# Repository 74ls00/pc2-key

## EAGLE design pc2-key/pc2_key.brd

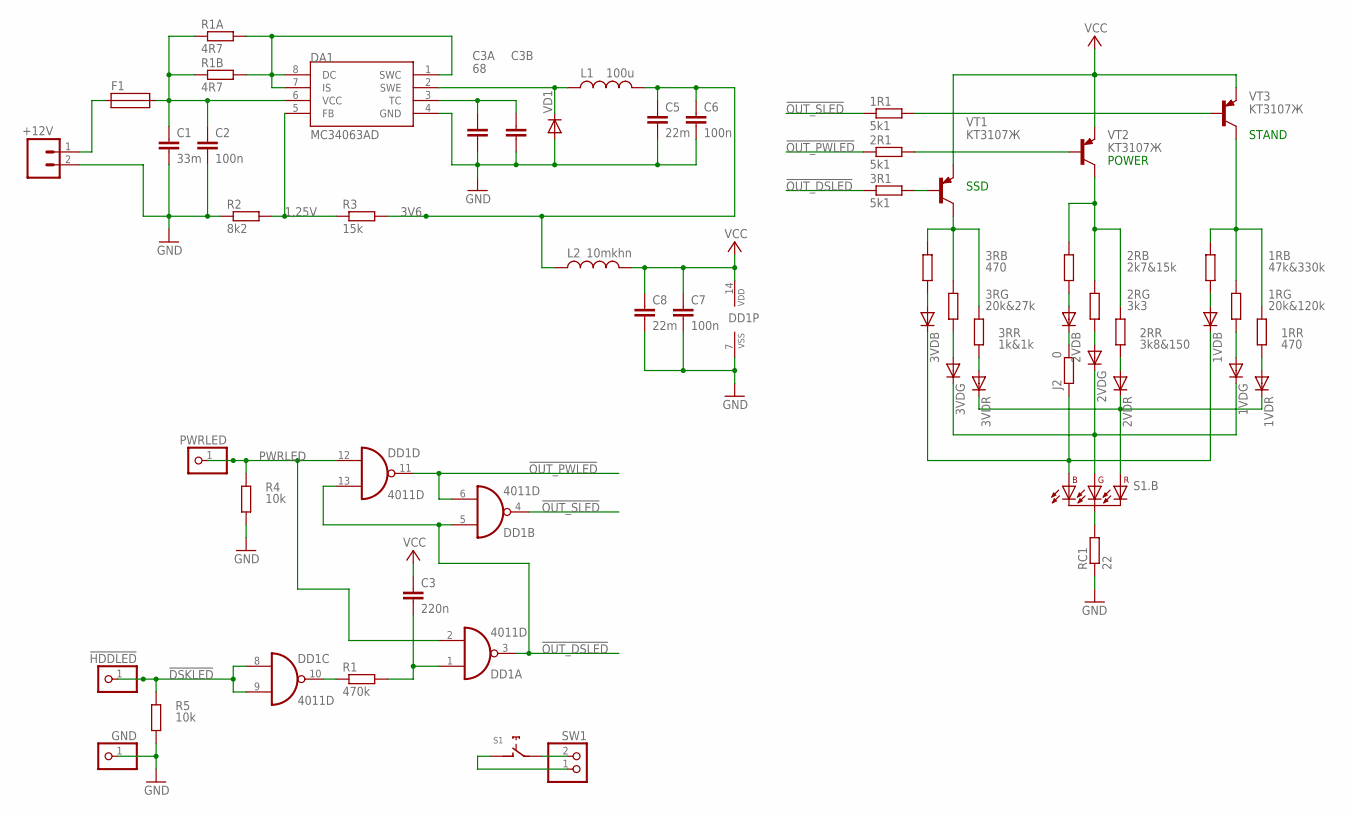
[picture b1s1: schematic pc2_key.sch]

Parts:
1R1, 2R1, 3R1: 5k1; R1206W
1RB: 47k&330k; R0805
1RG: 20k&120k; R0805
1RR, 3RB: 470; R0805
1VDB, 1VDG, 1VDR, 2VDB, 2VDG, 2VDR, 3VDB, 3VDG, 3VDR: DIODE-SOD80C; SOD80C
2RB: 2k7&15k; R0805
2RG: 3k3; R0805
2RR: 3k8&150; R0805
3RG: 20k&27k; R0805
3RR: 1k&1k; R0805
!HDDLED: PINHD-1X1; 1X01
+12V: CON_2P; CON_PWR_2PIN4MM
C1: 33m; C1210
C2, C6, C7: 100n; C0805K
C3: 220n; C0805
C3A: 68; C0805K
C3B: C-EUC0805K; C0805K
C5, C8: 22m; C1210
DA1: MC34063AD; SOIC8
DD1: 4011D; SO14
F1: SH32
GND: PINHD-1X1; 1X01
J2: 0; R1206W
L1: 100u; LH7X10MM
L2: 10mkhn; PIS2816
PWRLED: PINHD-1X1; 1X01
R1: 470k; M0805
R1A, R1B: 4R7; R1206
R2: 8k2; R0805
R3: 15k; R0805
R4: 10k; M0805
R5: 10k; R1206W
RC1: 22; R0805
S1: CHERRY-MX; CHERRY-MX-4P
SW1: PINHD-1X2; 1X02
VD1: DIODE-SMB; SMB
VT1, VT2, VT3: KT3107Ж; TO92

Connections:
1,25V: DA1.5 (FB), R2.2, R3.1
3V6: C5.1, C6.1, L1.1, L2.1, R3.2
!DSKLED: !HDDLED.1, DD1.8 (I0), DD1.9 (I1), R5.2
!OUT_DSLED: 3R1.1, DD1.3 (O), DD1.5 (I0), DD1.13 (I1)
!OUT_PWLED: 2R1.1, DD1.6 (I1), DD1.11 (O)
!OUT_SLED: 1R1.1, DD1.4 (O)
B: 1VDB.C, 3VDB.C, J2.1, S1.D1 (B)
G: 1VDG.C, 2VDG.C, 3VDG.C, S1.D2 (G)
GND: +12V.2, C1.2, C2.2, C3A.2, C3B.2, C5.2, C6.2, C7.2, C8.2, DA1.4 (GND), DD1.7 (VSS), GND.1, R2.1, R4.1, R5.1, RC1.1, VD1.A
unnamed: DA1.1 (SWC), DA1.7 (IS), DA1.8 (DC), R1A.2, R1B.2
unnamed: DD1.10 (O), R1.1
unnamed: C3A.1, C3B.1, DA1.3 (TC)
unnamed: 1RR.1, 1VDR.A
unnamed: 1RG.1, 1VDG.A
unnamed: 1RB.1, 1VDB.A
unnamed: 3R1.2, VT1.2 (B)
unnamed: 2R1.2, VT2.2 (B)
unnamed: 2RB.1, 2VDB.A
unnamed: 1R1.2, VT3.2 (B)
unnamed: C3.2, DD1.1 (I0), R1.2
unnamed: 2RR.1, 2VDR.A
unnamed: 2RG.1, 2VDG.A
unnamed: 3RR.1, 3VDR.A
unnamed: 3RG.1, 3VDG.A
unnamed: DA1.2 (SWE), L1.2, VD1.C
unnamed: 3RB.1, 3VDB.A
unnamed: S1.SW2, SW1.1
unnamed: S1.SW1, SW1.2
unnamed: RC1.2, S1.D3 (RGB-)
unnamed: 2VDB.C, J2.2
unnamed: 3RB.2, 3RG.2, 3RR.2, VT1.3 (C)
unnamed: 2RB.2, 2RG.2, 2RR.2, VT2.3 (C)
unnamed: 1RB.2, 1RG.2, 1RR.2, VT3.3 (C)
unnamed: C1.1, C2.1, DA1.6 (VCC), F1.P$2 (2A), R1A.1, R1B.1
unnamed: +12V.1, F1.P$1 (1A)
PWRLED: DD1.2 (I1), DD1.12 (I0), PWRLED.1, R4.2
R: 1VDR.C, 2VDR.C, 3VDR.C, S1.D4 (R)
VCC: C3.1, C7.1, C8.1, DD1.14 (VDD), L2.2, VT1.1 (E), VT2.1 (E), VT3.1 (E)

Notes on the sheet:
SSD
POWER
STAND

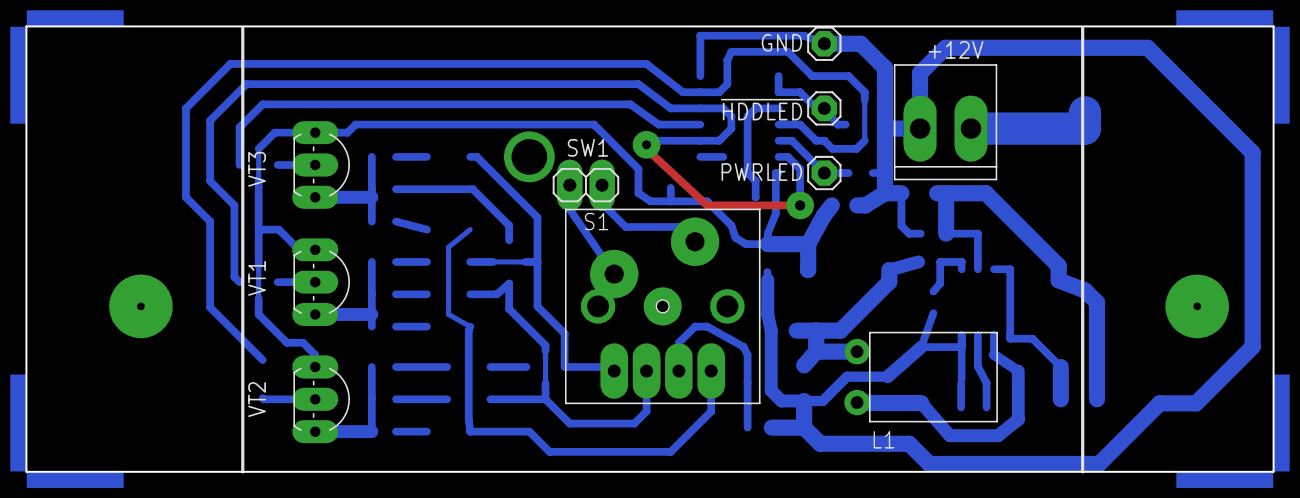
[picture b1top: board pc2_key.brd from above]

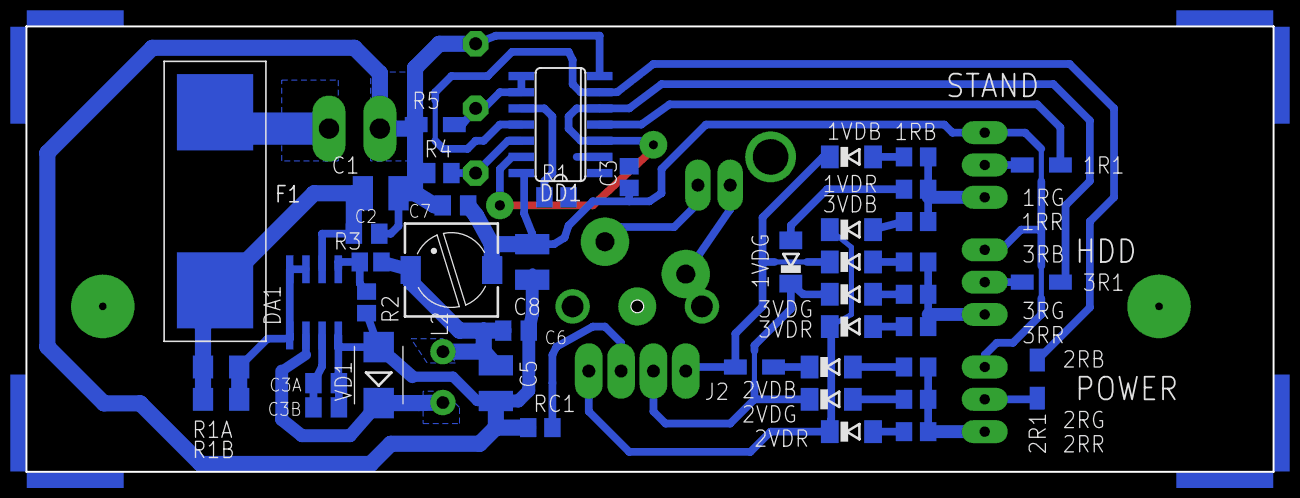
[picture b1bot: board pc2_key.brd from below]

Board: 2 copper layers, 98.0 x 35.0 mm, 58 parts (44 on the bottom side), 38 nets.

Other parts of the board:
U$5, U$6, U$7, U$8: ANGLE-SW-1
